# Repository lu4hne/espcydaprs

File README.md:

# ESP32 CYD (`ESP32-2432S024C` / `ESP32-2432S028R`) — Transceptor APRS 1200 bps / Tracker / Estación Fija + IGate + Estación Meteorológica WX (`v1.6.8`)

Aplicación completa de **codificación y decodificación APRS a 1200 baudios (AFSK Bell 202 / AX.25)** con **IGate APRS-IS bidireccional por WiFi**, **telemetría meteorológica I2C (`BME280 / BMP280`)** y **actualización de firmware por MicroSD y Web OTA**, diseñada para la familia de placas **ESP32 Cheap Yellow Display (CYD)** tanto en sus variantes con controlador **`ILI9341`** como **`ST7789` (1-USB)** y paneles táctiles **`CST820` (I2C)** o **`XPT2046` (SPI dedicado o compartido)**.

Permite conectar directamente un handy o base **Yaesu** o **Baofeng** (en VHF `144.390 MHz` / `144.930 MHz` o UHF) para operar tanto en terreno como **Tracker autónomo con GPS** como en el shack como **Estación Fija + IGate (RF $\leftrightarrow$ APRS-IS)**, **Estación Meteorológica APRS WX** y **Digipeater Fill-in `WIDE1-1`**.

> ### 🌐 Instalador Web Online (Sin Instalar Programas ni Compilar)
> Puedes grabar tu placa CYD o actualizarla a la última versión directamente desde tu navegador (**Google Chrome** o **Microsoft Edge**) entrando a:
> **👉 [https://lu4hne.github.io/espcydaprs/](https://lu4hne.github.io/espcydaprs/)**
> 
> *Incluye grabación con 1 clic por WebSerial, actualización rápida conservando tu indicativo y monitor serie en vivo para ver paquetes.*

> ### 🛰️ Nuevo Complemento: MicroTracker ESP32-C3 SuperMini (`MicroTracker/`)
> ¿Buscás un **tracker APRS ultracompacto sin pantalla** para llevar en bolsillo, bici o vehículo? Revisa el subproyecto **[MicroTracker/README.md](MicroTracker/README.md)** basado en **ESP32-C3 SuperMini** con GPS + SmartBeaconing™, portal de configuración WiFi bajo demanda, **botón SOS por hardware** y mensajería bidireccional por **Bluetooth BLE** mediante la **[Consola Móvil Web Bluetooth](https://lu4hne.github.io/espcydaprs/microtracker/)**.

---

## Características Principales

* **3 Modos de Operación Configurables en Pantalla o vía Web (`CONF 1/7` o toque rápido en `PANEL`):**
  1. **`MODO TRACKER (Móvil / Portátil RF)`:**
     * Diseñado para operación vehicular o portátil con **GPS Externo NMEA** (`UART2`) o posición fija, SSID sugerido `-9` / `-7`, símbolo de vehículo (`/>`) o handy (`/[`).
     * Transmite balizas periódicas por RF (`1200 bps AFSK`) manteniendo el WiFi apagado para ahorrar batería.
     * **Acceso Exclusivo al Botón `[SOS]`:** En la barra inferior del panel se añade el botón de emergencia rápida.
  2. **`MODO ESTACIÓN FIJA + IGATE (RF <-> APRS-IS)`:**
     * Conecta por WiFi al servidor **APRS-IS** (por defecto `samerica.aprs2.net:14580` o `rotate.aprs2.net:14580`) con filtro activo de radio y mensajería (`filter r/lat/lon/100 g/CALL* b/CALL*`).
     * **Cálculo automático de Passcode APRS-IS** a partir de tu indicativo (`CALLSIGN`), con opción de ingreso manual.
     * **Inyección RF $\rightarrow$ APRS-IS (`qAR`):** Todo paquete AX.25/APRS válido decodificado desde el radio VHF/UHF se inyecta en tiempo real a la red mundial APRS-IS (visible en `aprs.fi` y `aprsdirect.com`).
     * **Mensajería Bidireccional APRS-IS $\leftrightarrow$ RF (`MSJS`):** Envía y recibe mensajes directos con confirmación **`ACK`**, auto-respuesta de `ACK` al recibir mensajes dirigidos a tu indicativo, botón de respuesta rápida tocando cualquier mensaje recibido y reintentos automáticos.
     * **Baliza de Estación Fija Configurable:** Permite emitir tu posición fija por **`RF + APRS-IS`**, **`SOLO APRS-IS (Internet)`** o **`SOLO RF`**.
  3. **`MODO ESTACIÓN FIJA SOLO RF / DIGIPEATER`:**
     * Ideal para estaciones base o repetidoras de campaña sin acceso a Internet, con soporte para **Digipeater Fill-in `WIDE1-1`**.
* **Sistema de Aviso de Emergencia APRS (`\!` — SOS / Auxilio Exclusivo en Modo Tracker):**
  * **Restricción Estricta de Modo:** Disponible **únicamente en `MODO TRACKER`** (el botón `[SOS]` permanece completamente oculto e inactivo en modo Estación Fija e IGate). Si se conmuta a otro modo con una emergencia activa, se cancela y normaliza automáticamente.
  * **Mecanismo Anti-Error de 3 Toques con Timeout:** Al presionar `[SOS]` se despliega un diálogo modal de advertencia que requiere tocar un botón de confirmación **3 veces consecutivas** dentro de una ventana de **5 segundos** (mostrada con barra regresiva). Si no se completan los 3 toques dentro del límite, el diálogo expira y se cierra sin transmitir nada.
  * **4 Categorías de Incidente:** Selector táctil para indicar el tipo de auxilio: **`SOS Gen`**, **`Médico`**, **`Vehículo`** o **`Extravío`**.
  * **Protocolo Oficial APRS 1.0.1 (`\!`):** Emite balizas periódicas con tabla `\` y símbolo `!` (**`\!`**), activando de inmediato el octágono rojo de emergencia en plataformas como `aprs.fi` y `APRS-IS`, incluyendo coordenadas GPS/fijas, altitud y comentario descriptivo del incidente.
  * **Cancelación Inmediata con Trama de Resolución:** Pantalla dedicada de alerta activa con botón destacado **`[CANCELAR EMERGENCIA]`**, que al confirmarse transmite instantáneamente una baliza de resolución (`[EMERGENCIA CANCELADA - SITUACION NORMALIZADA]`) restaurando el símbolo original del operador.
  * **Configuración Avanzada (`CONF 6/7: SOS / EMERGENCIA` y Portal Web):**
    * **Intervalo de Baliza SOS:** `120 s` por defecto (opciones: `60 s`, `120 s`, `180 s`).
    * **Mensaje Directo APRS SOS:** Opcional (`SI` / `NO`) con indicativo destinatario configurable (ej. para avisar directamente a tu estación base o grupo de rescate).
    * **Alerta Sonora Parlante (`GPIO 26`):** Opcional (`SI` / `NO`), emite una sirena de 2 tonos cada 15 segundos por el altavoz integrado (silenciosa por defecto para no agotar la batería).
* **Sensor Meteorológico I2C (`CONF 5/7: SENSOR CLIMA` — `BME280 / BMP280`):**
  * Soporte dedicado y probado por **I2C por hardware** para **`BME280`** (Temperatura + Humedad + Presión) y **`BMP280`** (Temperatura + Presión) en `0x76` / `0x77`, sin interferir con la prioridad de recepción RF.
  * **Exclusión mutua estricta con GPS:** Por compartir los pines `IO16/IO17` del conector `P3`, el firmware impide activar simultáneamente **GPS externo (`Pos: GPS`)** y **Sensor Clima (`BME280/BMP280`)** tanto en la pantalla táctil como en el Portal Web, mostrando un aviso claro para evitar confusiones.
  * **Omisión Automática si no hay Sensor Conectado:** Si el sensor está en `APAGADO` o físicamente desconectado, **no se incluye ningún dato meteorológico en las balizas APRS**.
  * **3 Modos de Inclusión en Baliza APRS:**
    1. **`COMENTARIO`:** Añade al final de tu comentario las lecturas disponibles (ej: `24.5C 48% 1013hPa` en `BME280` o `24.5C 1013hPa` en `BMP280`).
    2. **`WX OFICIAL (/_)`:** Formatea la baliza con el estándar meteorológico APRS (`_.../...g...t076h48b10132`) para que `aprs.fi` grafique las curvas de temperatura, humedad y presión atmosférica.
    3. **`NO INFORMAR`:** Muestra temperatura, humedad y presión únicamente en la pantalla (`PANEL` y `CONF 5/7`), sin transmitirlas en las balizas.
* **Control de Brillo de Pantalla TFT y LED Azul de Estado (`CONF 7/7: CREDITOS Y VERSION`):**
  * Ajuste de brillo de retroiluminación **TFT (`100%`, `65%`, `35%`, `15%`)** por PWM y control del **LED Azul (`TENUE`, `MEDIO`, `OFF`)** guardado en memoria permanente NVS.
* **Actualización de Firmware por MicroSD y OTA (`CONF 4/7`):**
  * **Auto-Actualización por MicroSD en Arranque:** Si insertas una tarjeta MicroSD con `/update.bin` o `/firmware.bin`, la placa lo detecta al encender, muestra la barra de progreso en pantalla, actualiza la Flash y renombra el archivo a `/update.bak` para evitar bucles.
  * **Escáner e Instalador MicroSD en Pantalla:** En `CONF 4/7` puedes pulsar **`[ESCANEAR SD]`** para listar archivos `.bin` en la tarjeta e instalarlos con un toque.
  * **Portal Web Local + Subida OTA por Navegador (`WebServer` + `ArduinoOTA`):** En modo IGate (o pulsando **`[PORTAL WEB / AP WIFI OTA]`** que levanta la red WiFi `CYD-APRS-<INDICATIVO>` en `http://192.168.4.1`), puedes configurar toda la estación o subir un archivo `firmware.bin` desde el celular o PC (`http://<IP>/update`).
  * **Actualización Remota HTTP/HTTPS (`OTA URL`):** Descarga directa desde URL `.bin` o servidor con manifiesto JSON y validación de versión semántica (`SemVer`).
* **Módem DSP AFSK 1200 bps (Bell 202) en Tiempo Real (`Core 0`):**
  * **Modulador TX:** Síntesis Digital Directa (DDS) de fase continua para tonos **Mark (`1200 Hz`)** y **Space (`2200 Hz`)** en `GPIO 26` (`DAC2`) y en el pin de expansión seleccionado (`IO4`, `IO27`, `IO21` o `IO17`) mediante modulador Sigma-Delta a `312.5 kHz`, con codificación NRZI, *bit-stuffing* HDLC, `CRC-16 CCITT` y control automático de PTT (`GPIO 22`).
  * **Demodulador RX Universal (Equipos Comerciales y Radiosondas RS41):** Muestreo ADC continuo (`GPIO 35`) a `9600 Hz`, filtro eliminador de continua (DC blocker), correlador en cuadratura óptimo (*Matched Filter* con detección de 1200/2200 Hz balanceada 1:1), lazo **DPLL**, compuerta de nivel de ruido (squelch digital), validación `CRC-16` y decodificación tanto de tramas estándar como **Comprimidas Base-91** y telemetría de radiosondas (`RS41ng`).
  * **Modo Test Loopback Integrado:** Prueba la codificación y decodificación AX.25/APRS directamente en la placa con un toque en pantalla.

---

## Arquitectura del Proyecto

```text
espcydaprs/
├── platformio.ini          # Configuración PlatformIO (min_spiffs.csv, TFT_eSPI, TinyGPS++, ArduinoJson)
├── include/
│   ├── config.h            # Pinout de hardware (Radio, GPS, Sensores, MicroSD), modos y estructura NVS
│   ├── cst820_touch.h      # Driver multi-touch auto-detectado (CST820 I2C + XPT2046 SPI dedicado/HSPI)
│   ├── afsk_modem.h        # Módem DSP Bell 202 (1200/2200 Hz, NRZI, HDLC, CRC-16)
│   ├── ax25_aprs.h         # Codificador/Decodificador AX.25, parser APRS, GPS, WX y modos
│   ├── sensor_manager.h    # Driver nativo I2C/1-Wire para BMP280, BME280, AHT10/20, DHT22 y DHT11
│   ├── igate_manager.h     # Cliente TCP APRS-IS (inyección qAR, Passcode hash, filtros IS<->RF)
│   ├── update_manager.h    # Actualizador por MicroSD, HTTP/HTTPS OTA y Portal Web / AP
│   └── ui_manager.h        # Interfaz gráfica táctil de 5 pestañas de radio + 7 páginas Config + QWERTY
└── src/
    ├── main.cpp            # Inicialización dual-core, PWM Backlight/LED, auto-update SD y comandos Serial
    ├── cst820_touch.cpp    # Implementación de controladores táctiles CST820 y XPT2046
    ├── afsk_modem.cpp      # Procesamiento digital de señales (Core 0 a 9600 Hz)
    ├── ax25_aprs.cpp       # Lógica APRS, telemetría WX, mensajería con ACK, Haversine y NVS
    ├── sensor_manager.cpp  # Lectura y calibración de sensores meteorológicos I2C / DHT
    ├── igate_manager.cpp   # Gestión WiFi, login APRS-IS e inyección/recepción de paquetes
    ├── update_manager.cpp  # Flasheo desde MicroSD (VSPI) y OTA Web
    └── ui_manager.cpp      # Renderizado TFT_eSPI y eventos táctiles (Core 1)
```

---

## Pinout en las Placas CYD (Modelos `ILI9341` y `ST7789`)

### ¿Por qué no aparece `IO26` en los conectores laterales de la CYD?
En todas las variantes de la familia **CYD (`ESP32-2432S028R`, `ESP32-2432S024C`, etc.)**, el pin **`GPIO 26` (`DAC2`)** **no sale a los conectores blancos de expansión (`P3` / `CN1`)** porque está cableado internamente en el PCB a la entrada (`pin 4 IN-`) del amplificador de audio integrado **`SC8002B` / `FM8002A`**, cuya salida va al conector blanco de 2 pines **`SPK` (`P4`)**.

Para resolver esto sin necesidad de soldar sobre el integrado, el firmware genera la onda senoidal AFSK (`1200 / 2200 Hz`) **simultáneamente por dos vías**:
1. **Por un pin libre de tus conectores blancos de expansión** (`IO4`, `IO27`, `IO21` o `IO17`, seleccionable en pantalla) usando el modulador hardware **Sigma-Delta DAC del ESP32 a `312.5 kHz`** (que al finalizar la transmisión vuelve a `HIGH` en reposo para cero ruido en recepción y sin encender el LED RGB activo en bajo).
2. **Por `GPIO 26` (`DAC2`)** hacia el conector `SPK` (por si en algún momento deseas tomar audio analógico de `IO26`).

---

### Tabla de Conexiones según tu Modelo de Placa CYD

Puedes cambiar entre ambos modelos en cualquier momento desde **`CONF` -> `PAG 2/5`**, manteniendo presionado el botón físico **`BOOT` durante 2 segundos**, enviando la letra **`d`** por el monitor serie USB o desde el **Portal Web**:

#### Modelo A: Placa CYD con Driver `ILI9341`
*(Conectores expuestos: `IO35`, `IO22`, `IO21`, `IO27`, `TX`, `RX`)*

| Función | Pin a Usar | Comentario / Ubicación |
| :--- | :---: | :--- |
| **Audio RX (desde SPK Radio)** | **`IO35`** | Conector `P3` (`ADC1_CH7` - Solo entrada analógica). |
| **Control PTT Radio** | **`IO22`** | Conector `CN1` / `P3` (Salida `3.3V` en TX, `0V` en RX). |
| **Audio TX (hacia MIC Radio)** | **`IO27`** *(o `IO21`)* | Conector `CN1` / `P3` (DAC Sigma-Delta `312.5 kHz`). Si tu placa usa `IO21` para el Backlight, usa **`IO27`** para TX (por defecto); si usa `IO27` para Backlight, selecciona **`IO21`** en `CONF 2/5`. |
| **Backlight Pantalla TFT** | **`IO21` / `IO27`** | El firmware controla por PWM únicamente el pin que corresponde al Backlight de la pantalla. |
| **Tierra Común** | **`GND`** | Conector `P3` / `CN1`. |

#### Modelo B: Placa CYD con Driver `ST7789` (1 solo USB)
*(Conectores expuestos: `IO35`, `IO22`, `IO21`, `IO4`, `IO16`, `IO17`, `TX`, `RX`)*

| Función | Pin a Usar | Comentario / Ubicación |
| :--- | :---: | :--- |
| **Audio RX (desde SPK Radio)** | **`IO35`** | Conector `P3` (`ADC1_CH7` - Solo entrada analógica). |
| **Control PTT Radio** | **`IO22`** | Conector `CN1` / `P3` (Salida `3.3V` en TX, `0V` en RX). |
| **Audio TX (hacia MIC Radio)** | **`IO21`** | Conector `CN1` / `P3` junto a `IO22` (DAC Sigma-Delta `312.5 kHz`). Al elegir `Placa: ST7789` se asigna **`IO21`** automáticamente, dejando `IO27` para el Backlight TFT y `IO16`/`IO17` libres en `P3` para **Sensores I2C/DHT** o **GPS**. |
| **Sensores I2C / DHT (o GPS)** | **`IO16` / `IO17`** | Conector `P3`: `SDA = IO16`, `SCL = IO17` (o `DATA = IO17` para `DHT22/11`), o bien `UART2` si se usa GPS externo en modo `Pos: GPS`. |
| **Backlight Pantalla TFT** | **`IO27`** | Iluminación de pantalla TFT con brillo regulable (`100% / 65% / 35% / 15%`) en `CONF 6/6`. |
| **MicroSD (`CS / SCK / MISO / MOSI`)** | **`5 / 18 / 19 / 23`** | Zócalo MicroSD integrado (Bus VSPI). |
| **Tierra Común** | **`GND`** | Conector `P3` / `CN1`. |

---

### Relación entre el LED RGB Trasero y el Conector `P3` (`IO4`, `IO16`, `IO17`)

En el diseño electrónico de fábrica de la placa CYD, el **LED RGB trasero** (activo en `LOW`, es decir, enciende cuando el pin baja a `0V` y se apaga en `3.3V`) está conectado **en paralelo** con los 3 pines del conector blanco de expansión **`P3`**:

| Pin del ESP32 | Color en el LED RGB (Activo en `LOW`) | Función en el Conector `P3` (`Placa: ST7789`) | Comportamiento en el Firmware |
| :---: | :---: | :--- | :--- |
| **`GPIO 4`** | **Rojo** | **LED Indicador de TX** | Permanece en `HIGH` (`3.3V`, apagado) en recepción y se enciende en **Rojo** únicamente mientras el equipo está transmitiendo por radio (`PTT` activo). |
| **`GPIO 16`** | **Verde** | **Sensor `SDA`** *(o GPS TX)* | En modo I2C mantiene pull-up a `3.3V` (LED Verde apagado; solo destella brevemente al leer el sensor cada 5 s). |
| **`GPIO 17`** | **Azul** | **Sensor `SCL` / `DHT`** *(o GPS RX)* | Si no usas sensores ni GPS en `IO17`, funciona como indicador de **IGate Conectado** con brillo regulable (`TENUE / MEDIO / OFF`) desde `CONF 6/6`. Si activas un sensor en `P3`, `IO17` pasa automáticamente a ser el reloj `SCL` (con pull-up a `3.3V`). |

---

### ¿Qué son los `ms` de Delay (`Dly: xxx ms` / `TX Delay`) en `CONF 2/6`?

Sí: el parámetro **`Dly: xxx ms` (`TX Delay`)** define el tiempo de **preámbulo desde que se activa el PTT (`GPIO 22 = HIGH`) hasta que comienza a enviarse la información real del paquete AX.25**:
1. Al iniciar una transmisión, el ESP32 levanta inmediatamente el **PTT (`IO22`)** para poner el handy en transmisión.
2. Durante los **`ms` configurados en `Dly`** (por ejemplo `450 ms` en el preset **`BAOFENG`** o `250 ms` en **`YAESU`**), el módem envía por **`IO21`** una ráfaga continua de **banderas de sincronización HDLC (`0x7E`, tonos alternados `1200/2200 Hz`)**.
3. Esto permite que:
   * Tu transmisor estabilice la portadora RF.
   * El receptor del otro corresponsal (o del IGate/Digipeater) alcance a abrir su *squelch*, despertar del ahorro de batería (*Battery Save* de los Baofeng) y sincronizar su reloj digital (DPLL) antes de que llegue la primera letra de tu indicativo.
4. Al terminar el paquete y su `CRC-16`, transmite `~60 ms` adicionales de cola (`TX Tail`) y suelta el PTT.

---

## Conexión del Sensor Meteorológico I2C (`CONF 5/7` — `BME280 / BMP280`)

El firmware soporta de forma exclusiva y estable el sensor **I2C por hardware `BME280` / `BMP280`** (sin interrupciones de software que afecten al módem AFSK):

| Chip Detectado | Dirección I2C | Magnitudes Medidas | Nota Técnica |
| :--- | :---: | :--- | :--- |
| **`BME280`** *(Recomendado)* | `0x76` / `0x77` | Temperatura (`°C`) + Humedad (`%`) + Presión (`hPa`) | Estación meteorológica APRS WX completa en un solo módulo de 4 pines. |
| **`BMP280`** | `0x76` / `0x77` | Temperatura (`°C`) + Presión (`hPa`) | Mismo módulo de 4 pines (omite humedad). |

> **Importante — Exclusión mutua con GPS:** El sensor I2C y el GPS UART2 comparten el conector `P3` (`IO16/IO17`). Para usar el sensor `BME280/BMP280`, la estación debe estar en **`Pos: FIJA`** (`CONF 1/7`). Si activas `Pos: GPS` o cambias a `MODO TRACKER`, el sensor se bloquea/apaga automáticamente.

### Cableado en el Conector Blanco `P3` (`I2C: SDA=16 SCL=17`)

| Pin del Sensor (`BME280 / BMP280`) | Pin en la Placa CYD (`Conector P3`) |
| :---: | :--- |
| **`VCC` / `VIN`** | **`3.3V`** |
| **`GND`** | **`GND`** |
| **`SDA`** | **`IO16`** |
| **`SCL`** | **`IO17`** |

*(También puedes seleccionar en `CONF 5/7` los perfiles alternativos `SDA=21 SCL=22` o `SDA=27 SCL=22` según los pines libres de tu placa).*

### ¿Qué ocurre si el sensor no está conectado?
* Si dejas `Sensor: APAGADO` (valor por defecto) o el sensor **no está físicamente conectado**, **las balizas APRS no incluyen ningún dato meteorológico** y se transmiten únicamente con tu posición y comentario normal.

---

## Circuito de Interfaz entre el ESP32 y el Radio (Baofeng / Yaesu)

Para acoplar el audio sin saturar el micrófono del radio ni dañar el ADC del ESP32 con voltajes negativos, arma esta sencilla interfaz en una pequeña placa perforada:

### Esquema Eléctrico Completo

```text
================================================================================
1. ENTRADA DE AUDIO RX (Salida Auricular/SPK del Radio ---> IO35 del ESP32)
================================================================================

                  +3.3V (ESP32)
                     |
                    [R1] 10 kΩ
                     |
SPK Radio o---||-----+----------+-----> IO35 (ADC1_CH7)
             C1      |          |
            1 µF    [R2] 10 kΩ === C2 (10nf) 
                     |          |
                    GND        GND (Común)

* R1 y R2 (10 kΩ) crean un punto medio de 1.65V DC para que la onda de audio
  oscile entre 0V y 3.3V sin recortarse.
* C1 (1 µF cerámico o electrolítico) aísla el nivel DC del amplificador del radio.
* C2 (10 nF cerámico "103") en paralelo con R2 forma un filtro pasa-bajos pasivo
  con frecuencia de corte en ~3.1 kHz, eliminando el siseo y ruido blanco de alta frecuencia al abrir el squelch para una decodificación AFSK óptima y estable.

================================================================================
2. SALIDA DE AUDIO TX (IO4 / IO27 / IO21 / IO17 ---> Entrada MIC del Radio)
================================================================================

                                             C2 (1 µF)
Pin TX (IO4 o IO27) o---[R3 10 kΩ]---+---+------||--------> Entrada MIC del Radio
                                     |   |
                            [R4] 1 kΩ   === C3 (10 nF a 100 nF cerámico "103"/"104")
                                     |   |
                                    GND GND (Común)

* R3 (10 kΩ) y R4 (1 kΩ) forman un atenuador ~10:1 que reduce los ~2.5 Vpp a
  ~200 mVpp (nivel ideal de micrófono electret para Yaesu y Baofeng).
* R3 (10 kΩ) + C3 (10 nF a 100 nF en paralelo con R4) forman además el filtro
  pasa-bajos RC que elimina por completo la portadora Sigma-Delta de 312.5 kHz,
  entregando una onda senoidal pura de 1200 / 2200 Hz.
* C2 (1 µF) bloquea los +5V/+8V de alimentación fantasma (bias) del micrófono.

================================================================================
3. CONTROL DE PTT (IO22 del ESP32 ---> Línea PTT del Radio)
================================================================================

                               Colector
                                  |-------------> Pin PTT del Radio
IO22 o-------[R5 2.2 kΩ]----|  2N2222 / BC548
                            |     |
                             \    v Emisor
                                  |
                                 GND (Común)
```

### Versión Mejorada de Filtros de Audio (Recomendada para PCB / Montaje Definitivo)

Para obtener tonos TX aún más limpios (sin atenuar `2200 Hz` y con rechazo >55 dB de la portadora Sigma-Delta de `312.5 kHz`), ajuste fino de desviación FM y máxima protección/rechazo de ruido en la entrada RX (compatible 100% con el firmware actual en `ADC 12 dB / 0–3.3V`):

```text
================================================================================
1B. ENTRADA DE AUDIO RX MEJORADA (Filtrado de Vref + Protección Diodos)
================================================================================

  +3.3V o---[R5 100 Ω]---+----+----+-----> Vref (~3.3V filtrado)
                         |    |    |
                        ===  ===  [R6 10 kΩ]
                    C4 100nF C5 22µF |
                         |    |      |
                        GND  GND     +----|<|----+ (D1: 1N4148 ánodo al ADC, cátodo a Vref)
                                     |           |
  SPK Radio o---||-------------------+-----------+---> IO35 (ADC1_CH7, ~1.65V DC)
               C6 4.7 µF             |           |
                                 [R9 10 kΩ]     =|= (D2: 1N4148 cátodo al ADC, ánodo a GND)
                                     |           |
                                    GND         GND (Común)

* R5 (100 Ω) + C4 (100 nF) + C5 (22 µF) filtran el ruido de la fuente 3.3V
  (USB, WiFi y TFT) antes de polarizar el ADC en 1.65V.
* D1 y D2 (1N4148) protegen IO35 contra picos de volumen altos del parlante.
* Opcional: si el volumen de tu handy resulta demasiado sensible, agrega un
  divisor resistivo (3 kΩ en serie + 1 kΩ a GND) antes de C6.

================================================================================
2B. SALIDA DE AUDIO TX MEJORADA (Filtro Pasabajos 2 Polos + Preset VR1K)
================================================================================

  Pin TX o---[1.5 kΩ]---+---[1.5 kΩ]---+---[R1 22 kΩ*]---+
                        |              |                 |
                       === C3         === C2           [VR1K] (Preset 1 kΩ)
                      10 nF          10 nF              /  |---> [C1 1 µF] ---> MIC Radio
                        |              |                |
                       GND            GND              GND (Común)

* Doble etapa RC (1.5 kΩ + 10 nF x2): respuesta plana en 1200/2200 Hz y
  atenuación >55 dB sobre la portadora Sigma-Delta de 312.5 kHz.
* *R1: usar 47–68 kΩ para handies de micrófono muy sensible (Baofeng) o
  15–22 kΩ para equipos Yaesu / base; calibrar desviación fina con VR1K.
* Mantener siempre el transistor NPN (2N2222/BC547) en la línea PTT (IO22).
```

---

## Guía de Uso en la Pantalla Táctil (`5 Pestañas Inferiores + 6 Páginas de Configuración`)

La barra inferior mantiene **5 botones amplios dedicados a la operación de radio** y unifica todos los ajustes dentro de **`CONF`**:

1. **`PANEL` (Dashboard Principal de Radio):**
   * Muestra tu indicativo (`LU4HNE-7` / `LU4HNE-10`), el **Modo Activo** (`MODO: TRACKER RF`, `MODO: FIJA + IGATE` o `MODO: FIJA SOLO RF`), estado de posición (`POS:FIJA` o `GPS:xSAT`), estado de conexión **APRS-IS** (`IG:ON` en verde cuando está verificado) y contadores `TX`, `RX` e `IG`.
   * Si hay un sensor meteorológico conectado, muestra en vivo las lecturas de clima (`WX: 24.5C | 1013.2 hPa`).
   * **Cambio rápido de modo:** Toca la tarjeta superior izquierda en `PANEL` para alternar entre **Tracker**, **Estación Fija + IGate** y **Fija Solo RF**.
   * **Barra `AUDIO RX` (Vúmetro en vivo):** Ajusta el volumen de tu handy hasta que al recibir una señal el vúmetro se mantenga en la **zona verde (`30%` a `80%`)**.
   * **`[TX BALIZA]` / `[LOOPBACK]` / `[AUTO]`:** Transmite baliza inmediata (por RF y/o APRS-IS), ejecuta autodiagnóstico en bucle cerrado o activa el temporizador automático.
2. **`MONIT` (Monitor de Tráfico AX.25 / IGate + Diagnóstico DSP Opcional):**
   * Lista en tiempo real de paquetes decodificados con distancia (`km`), rumbo cardinal y etiqueta verde **`[IGATE]`** cuando el paquete fue inyectado o recibido desde **APRS-IS**.
   * **Botón opcional `[DIAG]` (esquina superior derecha):** Apagado por defecto (sin impacto en rendimiento). Al activarlo reinicia los contadores y muestra en vivo las métricas del demodulador DSP sobre señales reales (`DC` de polarización ADC, porcentaje Mark `M%`, banderas `0x7E`, errores `CRC`, tramas abortadas y detección de `CLIPPING ADC` o ausencia de banderas).
   * **Arquitectura de Recepción Prioritaria RF (`v1.6.8`):** La tarea dedicada `AFSK_RX` corre en **Core 1 con prioridad máxima (`10`)** disparada por el **Timer de Hardware 3 (`104 µs` / `9600 Hz`)**, con demodulador DSP 100% entero y cola de `16` tramas, completamente aislada del stack WiFi/TCP-IP (Core 0) y sin pausas al conectar WiFi o abrir el Portal OTA. Incluye timeouts I2C (`50 ms`) en `Wire`/`Wire1` y sensor meteorológico en `APAGADO` por defecto.
3. **`MSJS` (Mensajes APRS Bidireccionales por RF y APRS-IS):**
   * Redacta mensajes con el teclado táctil QWERTY, con confirmación automática **`ACK`** y reintentos.
   * **Respuesta con un toque:** Toca cualquier mensaje recibido en la lista para abrir directamente la ventana de respuesta hacia ese corresponsal.
   * **Autoprueba de ACK:** Si envías un mensaje a tu propio indicativo (`LU4HNE-10`), el sistema valida el ciclo completo y confirma `ACK OK` en verde.
4. **`ESTAC` (Directorio de Estaciones Escuchadas):**
   * Lista de estaciones únicas con distancia, acimut, coordenadas y cantidad de paquetes.
5. **`CONF` (Configuración Unificada en 7 Páginas + Auto-Guardado en Flash NVS):**
   * **Página 1 (`1/7: MODO Y ESTACION`):** Selector de Rol (`TRACKER MOVIL`, `ESTACION FIJA + IGATE`, `ESTACION FIJA SOLO RF`), Indicativo, SSID (`-0` a `-15`), Símbolo (`IGate I&`, `Handy`, `Auto`, `Casa`, `Camión`), fuente de posición (`FIJA` / `GPS`), Latitud, Longitud y Comentario.
   * **Página 2 (`2/7: RADIO Y BALIZA`):** Modelo de Placa (`ILI9341` / `ST7789`), botón compacto **`NORM / INV`** para **inversión de colores TFT** (`TFT_INVOFF` / `TFT_INVON`, también configurable por comando serie `'i'`, toque rápido en `CONF 7/7` o desde el Portal Web OTA), **`TX Pin`**, selector de preset **`BAOFENG`** / **`YAESU`**, `TX Delay (ms)`, `Nivel TX (%)`, intervalo de baliza (`60s` a `900s`), `Auto-ACK` y `Digipeater WIDE1-1`.
   * **Página 3 (`3/7: WIFI E IGATE`):** SSID y Clave WiFi (con teclado alfanumérico + símbolos `#?=`), servidor APRS-IS (`rotate.aprs2.net` / `samerica.aprs2.net`), `Passcode` (calculado automáticamente desde tu indicativo o manual), modo de baliza IGate (`RF + IS`, `SOLO IS`, `SOLO RF`) y botón **`[CONECTAR]`**.
   * **Página 4 (`4/7: SD Y WEB OTA`):**
     * **`[ESCANEAR SD]` / `[INSTALAR SD]`:** Busca e instala archivos `.bin` desde la tarjeta MicroSD con barra de progreso en pantalla.
     * **`[OTA URL]`:** Descarga e instala actualizaciones remotas por HTTP/HTTPS.
     * **`[PORTAL WEB / AP WIFI OTA]`:** Inicia el servidor web de configuración (incluyendo inversión de color TFT) y actualización OTA en `http://<IP>` (o crea el punto de acceso WiFi `CYD-APRS-<INDICATIVO>` en `http://192.168.4.1`).
   * **Página 5 (`5/7: SENSOR CLIMA I2C`):**
     * Estado en vivo de **Temperatura (`°C`)**, **Humedad (`%`)** y **Presión (`hPa`)**.
     * Selector de **`Sensor`** (`APAGADO` / `BME/BMP280` por I2C hardware), **`Pines`** (`SDA=16 SCL=17`, `21/22`, `27/22`), modo de envío en **`Baliza`** (`COMENTARIO`, `WX OFICIAL /_`, `NO INFORMAR`), calibración de **`Offset Temp`** (`-0.5°C` / `+0.5°C`) y botón **`[DETECTAR]`**.
     * **Exclusión mutua con GPS:** Solo puede activarse con **`Pos: FIJA`**; si el GPS está activo, se bloquea con aviso en pantalla. Si el sensor no está conectado, las balizas APRS omiten automáticamente cualquier dato meteorológico.
   * **Página 6 (`6/7: EMERGENCIA SOS`):**
     * Intervalo de baliza SOS (`60s` / `120s` / `180s`), activación de mensaje directo de auxilio, destinatario (`CALLSIGN`) y alerta sonora por parlante.
   * **Página 7 (`7/7: CREDITOS Y VERSION` — Siempre la última página / About):**
     * Muestra créditos del proyecto (`LU4HNE`), versión instalada (`v1.6.8`), hardware activo (`Driver TFT` con indicador `(Inv)`, `Touch`, `Pin Audio TX`, `IP`, `Passcode` y memoria RAM libre). Tocar esta tarjeta alterna rápidamente la inversión de color de pantalla.
     * Incluye selectores de brillo del **LED Azul (`LED: TENUE / MEDIO / OFF`)**, brillo de pantalla **TFT (`TFT: 100% / 65% / 35% / 15%`)**, **`[GUARDAR]`** y **`[REINICIAR]`**.

---

## Demodulador DSP y Filtrado de Audio (1000 Hz a 2500 Hz)

El receptor AFSK a `1200 baudios` utiliza un **Filtro Adaptado en Cuadratura (*Matched Filter*)** a 9600 Hz con detección ortogonal ($I/Q$) sobre una ventana deslizante de 8 muestras:

1. **Rechazo Natural de Ruido Fuera de Banda (Filtro Pasabanda Intrínseco):**
   * El correlador DSP sintoniza por transformada exacta de Fourier las frecuencias centrales **`Mark (1200 Hz)`** y **`Space (2200 Hz)`**.
   * Las frecuencias fuera del rango útil son atenuadas naturalmente por el algoritmo:
     * Tonos sub-audibles CTCSS/PL (`67 Hz` a `250 Hz`): atenuación de **`-23 dB` a `-18 dB`**.
     * Ruido de conmutación y armónicos (`>3500 Hz`): atenuación superior a **`-15 dB`**.
   * Por esta razón **no es necesario un circuito activo complejo con amplificadores operacionales**.
2. **Filtro Pasabanda Pasivo Opcional de Entrada (Recomendado si hay mucho siseo):**
   * El circuito de entrada con capacitor $C_1$ (`1 µF`) y el divisor $R_1 / R_2$ (`10 kΩ` c/u) ya crea un filtro pasa-altos con corte en **`31.8 Hz`**.
   * Para limitar pasivamente las frecuencias altas y eliminar el siseo del receptor cuando abre el squelch, basta con soldar un pequeño **capacitor cerámico de `10 nF`** (marcado "103") o `22 nF` en paralelo con la resistencia $R_2$ (la que va a masa). Esto fija una frecuencia de corte superior en **`~3180 Hz`**, formando un filtro pasabanda pasivo completo sin componentes activos.
3. **Compuerta Digital de Ruido (Squelch DSP):**
   * Se evalúa el umbral mínimo de señal antes de alimentar transiciones al bucle DPLL y a la máquina de estados HDLC, impidiendo que el ruido blanco de canal genere falsas banderas (`0x7E`) que bloqueen la captura de balizas reales.
4. **Decodificación de Telemetría de Sondas (`WX`) y Coordenadas Comprimidas Base-91 (`ax25_aprs.cpp`):**
   * **Tramas Meteorológicas y de Radiosondas:** Reconoce y formatea automáticamente campos climáticos en paquetes de posición (`.../...g...t032h01b00000...` $\rightarrow$ `[0.0C 1%] RS41ng radiosonde firmware`), convirtiendo grados Fahrenheit a Celsius, humedad relativa (`%`) y presión barométrica (`hPa`).
   * **Filtro de Coordenadas Nulas (`0000.00S/00000.00W`):** Cuando una sonda o tracker transmite antes de adquirir satélites GPS (`Lat = 0.0, Lon = 0.0`), evita calcular una distancia falsa de `~6472 km` hacia el punto `(0°, 0°)`.
   * **Soporte Base-91 Comprimido (`/YYYYXXXX$csT`):** Decodifica latitud, longitud y altitud exponencial comprimida en Base-91, estándar muy utilizado en firmwares de radiosondas y trackers compactos.

---

## Compilación y Carga con PlatformIO

1. Para compilar el proyecto:
   ```bash
   pio run
   ```
2. Para subir por cable USB:
   ```bash
   pio run -t upload
   ```
3. Para actualizar por **Navegador Web (OTA)** o `curl`:
   * Abre `http://<IP_DE_LA_PLACA>/update` desde tu navegador y selecciona `.pio/build/esp32-2432s024c/firmware.bin`, o ejecuta:
     ```bash
     curl -F "update=@.pio/build/esp32-2432s024c/firmware.bin" http://<IP_DE_LA_PLACA>/update
     ```
4. Para actualizar por **MicroSD**:
   * Copia el archivo generado `.pio/build/esp32-2432s024c/firmware.bin` a la raíz de una tarjeta MicroSD FAT32 (como `/firmware.bin` o `/update.bin`).
   * Inserta la tarjeta en la placa CYD y reinicia (se instalará automáticamente al arrancar) o ve a **`CONF` -> `PAG 4/5` -> `[ESCANEAR SD]`**.

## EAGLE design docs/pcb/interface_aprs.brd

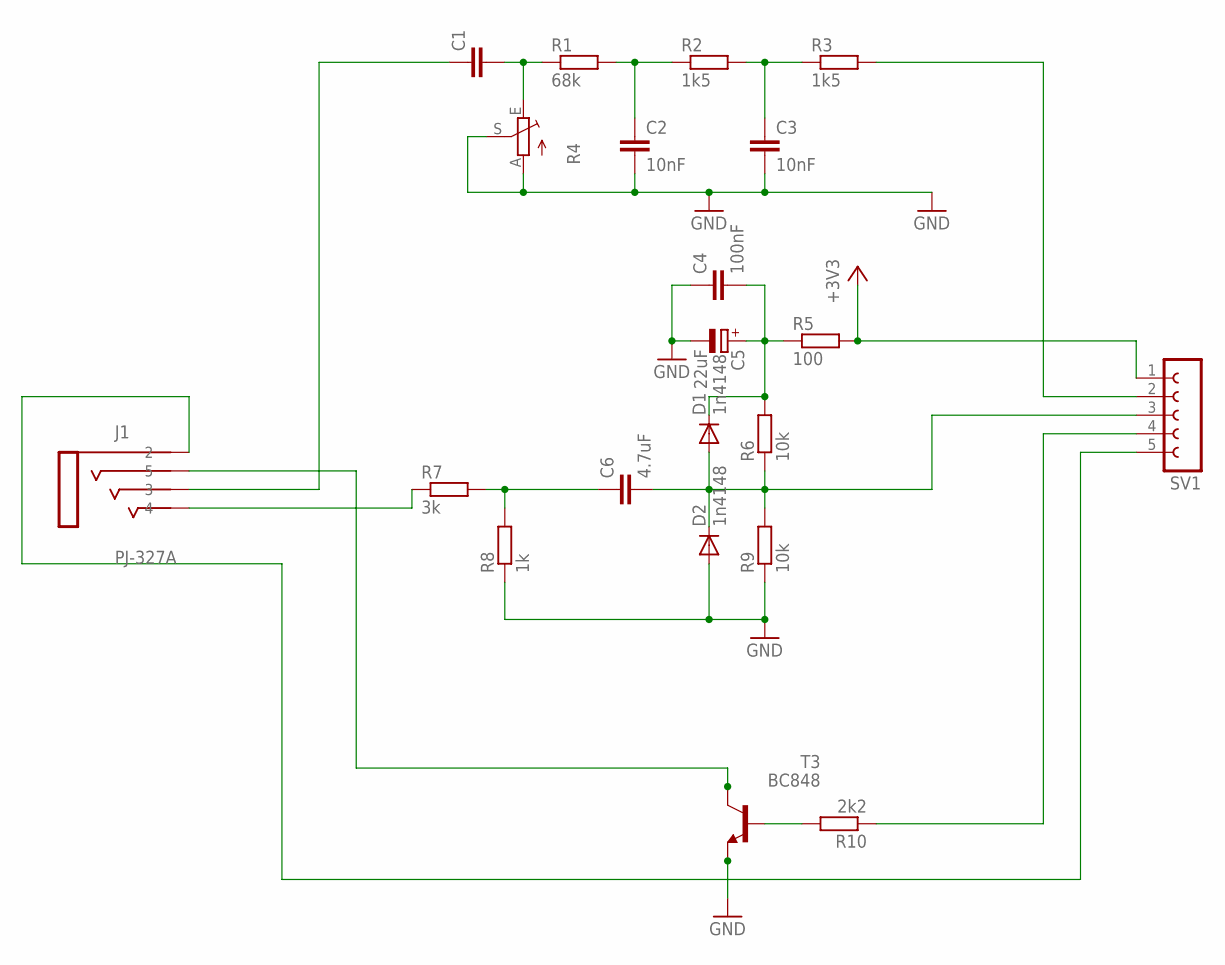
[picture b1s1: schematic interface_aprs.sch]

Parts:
C1: C-EUC0805; C0805
C2, C3: 10nF; C0805
C4: 100nF; C0805
C5: 22uF; B/3528-21R
C6: 4.7uF; C0805
D1, D2: 1n4148; DO214AA
J1: PJ-327A; PJ-327A_SMD
R1: 68k; R0805
R2, R3: 1k5; R0805
R4: TRIM_EU-B25P; B25P
R5: 100; R0805
R6, R9: 10k; R0805
R7: 3k; R0805
R8: 1k; R0805
R10: 2k2; R0805
SV1: FE05-1
T3: BC848; SOT23-BEC

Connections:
+3V3: R5.2, SV1.1
GND: C2.2, C3.2, C4.1, C5.-, D2.A, J1.2, R4.A, R4.S, R8.1, R9.1, SV1.5, T3.E
unnamed: C2.1, R1.2, R2.1
unnamed: C3.1, R2.2, R3.1
unnamed: C1.2, R1.1, R4.E
unnamed: C1.1, J1.3
unnamed: R10.2, T3.B
unnamed: C6.1, R7.2, R8.2
unnamed: C4.2, C5.+, D1.C, R5.1, R6.2
unnamed: C6.2, D1.A, D2.C, R6.1, R9.2, SV1.3
unnamed: J1.5, T3.C
unnamed: R10.1, SV1.4
unnamed: R3.2, SV1.2
unnamed: J1.4, R7.1

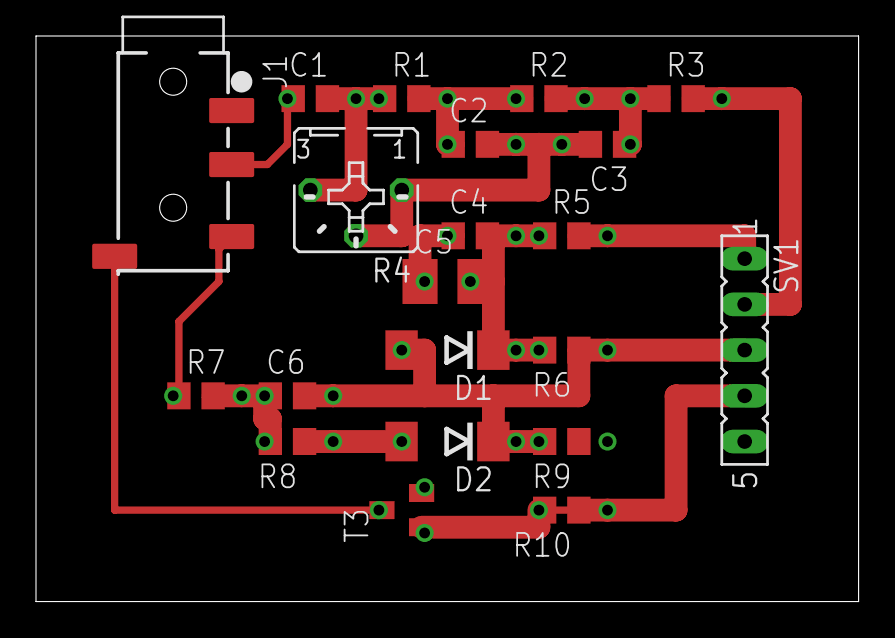
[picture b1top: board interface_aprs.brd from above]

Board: 2 copper layers, 45.7 x 31.4 mm, 21 parts (0 on the bottom side), 14 nets.
